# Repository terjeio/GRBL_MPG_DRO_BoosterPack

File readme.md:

## GRBL MPG & DRO BoosterPack for Tiva C \(TM4C123G\) and RP2040 (Pi Pico)

__2024-01-29:__ Added firmware and flasher code for the MSP430 keypad controller to the RP2040 version. This will check for and install/update the firmware automatically.  
Splitted LCD driver code in separate files for each display type supported.

__2022-01-13:__ Added wiring diagram for default key and LED map.

[Default wiring diagram (pdf)](media/Default%20keypad%20and%20LED%20wiring.pdf).  

The latest keypad code allows adding new keymappings at run time, switching between a few predefined ones or creating a new from scratch.

__2022-01-10:__ First preliminary version with Pi Pico support committed. Tiva C \(TM4C123\) version updated for new HAL/APIs.

__2021-08-30: Pi Pico breakout board design__

First batch of boards \(for final design verification\) to be ordered soon.

__2021-05-01: HALification of the code is underway__

A RP2040 driver for [Pi Pico](https://www.raspberrypi.org/products/raspberry-pi-pico/) is nearing completion, watch this space.

__2019-08-20: Improved startup sequence__

The GPIO line used for signalling MPG mode change is now used to signal the grbl controller ready state during startup.

On a cold start the Grbl microcontroller should pull the line low as early in the process as possible.
When the cold start sequence is completed and grbl is ready to receive data the line should be reverted to input mode with interrupt and pullup enabled.
The MPG microcontroller will wait for the line going high before starting any communication, displaying a progress indicator in its boot screen while waiting.

---

Features:

* SPI LCD and touch interface
* Up to two MPG wheels (QEI connected)
* Four GPIO pins, one is preassigned for switching grbl to/from MPG mode
* Up to 8 LEDs, buffered open drain 
* Feed Hold and Cycle Start outputs, open drain
* Up to 25 keys (in matrix)
* Navigator interface
* I2C port (3V3)
* On board MSP430G2553 handling keys and LEDs, internal I2C interface to Tiva C

Parts of alpha-version of supporting code is now available.
An initial commit of the [display driver](https://github.com/terjeio/Display-libraries/) used has now been made public.
The code is written so it is should be easy to port, all processor dependent code is in separate files. 

All core funtionality is now up and running, GUI is 100% event driven making it easy to extend with new dialogs. Shared dialogs (canvases) created for common data (such as DOC, feed rate, RPM), input review/confirmation and GCode transfer to grbl.

### How it works

The setup comprises 3 microcontrollers: one running Grbl, one handling the keyboard scanning and one (the MPG processor) for the DRO and MPG \(user interface\).

#### Grbl/grblHAL microcontroller:

Support for a second input stream and a switch for changing to/from MPG mode has to be added to the code.
In \"normal\" mode the MPG processor listen to the output stream from Grbl, parses the data and displays relevant info on the display.
In \"MPG\" mode Grbl switches its serial input to the second input stream and the MPG prosessor takes over control by acting as a GCode sender.
To tell the MPG processor about a mode change the real time report from Grbl is extended with |MPG:0 \(\"normal\"\) and |MPG:1 \(\"MPG\"\), this is only added when the mode change takes place.
Some of my [grblHAL drivers](https://github.com/grblHAL) supports this functionality as does my [patched version of grbl-Mega](https://github.com/terjeio/grbl-Mega).
 
#### MPG microcontroller:

This handles the user interface \(keypresses, MPG input, menu navigator input and DRO display\). In \"normal\" mode it passively listen to the output stream coming from Grbl, parses it and updates the display and LED statuses accordingly.
For this to work correctly there has to be a PC based GCode sender connected to the controller, such as [ioSender](https://github.com/terjeio/ioSender), that constantly request the real time status report.

In \"MPG\" mode it takes over control and acts as a GCode sender itself, ideally the PC based GCode sender should then disable its GUI.
When turning the MPG wheels G1 commands are issued with a feed rate that is dependent on the turning speed, simulating the action of the handwheels on the lathe.
The jog buttons issues jog commands and most of the other buttons issues real-time commands such as Hold or Cycle start. It is also possible to hardwire some of the button states to the corresponding Grbl input signals.

For the lathe version I am currently working on I am adding canvases \(or dialogs\) that will be used for some simple tasks such as reducing the diameter of the stock, and possibly threading if the Grbl version supports that.
There is a common canvas for streaming task data, this may be used to stream data from a SD card \(not yet implemented\). 

#### Keyboard handling microcontroller:

Due to limited IO on the MPG microcontroller a separate processor is employed for handling the keyboard and LEDs.
Up to 25 keys can be added (in a matrix) and 8 LEDs are supported. Keypresses are sent to the MPG controller via I2C, and there is a strobe signal for telling MPG controller that a key is pressed.
The strobe signal suppports different key modes such as single shot, autorepeat and continuous - configurable per key.

---

### Pi Pico breakout board

---
2021-08-30

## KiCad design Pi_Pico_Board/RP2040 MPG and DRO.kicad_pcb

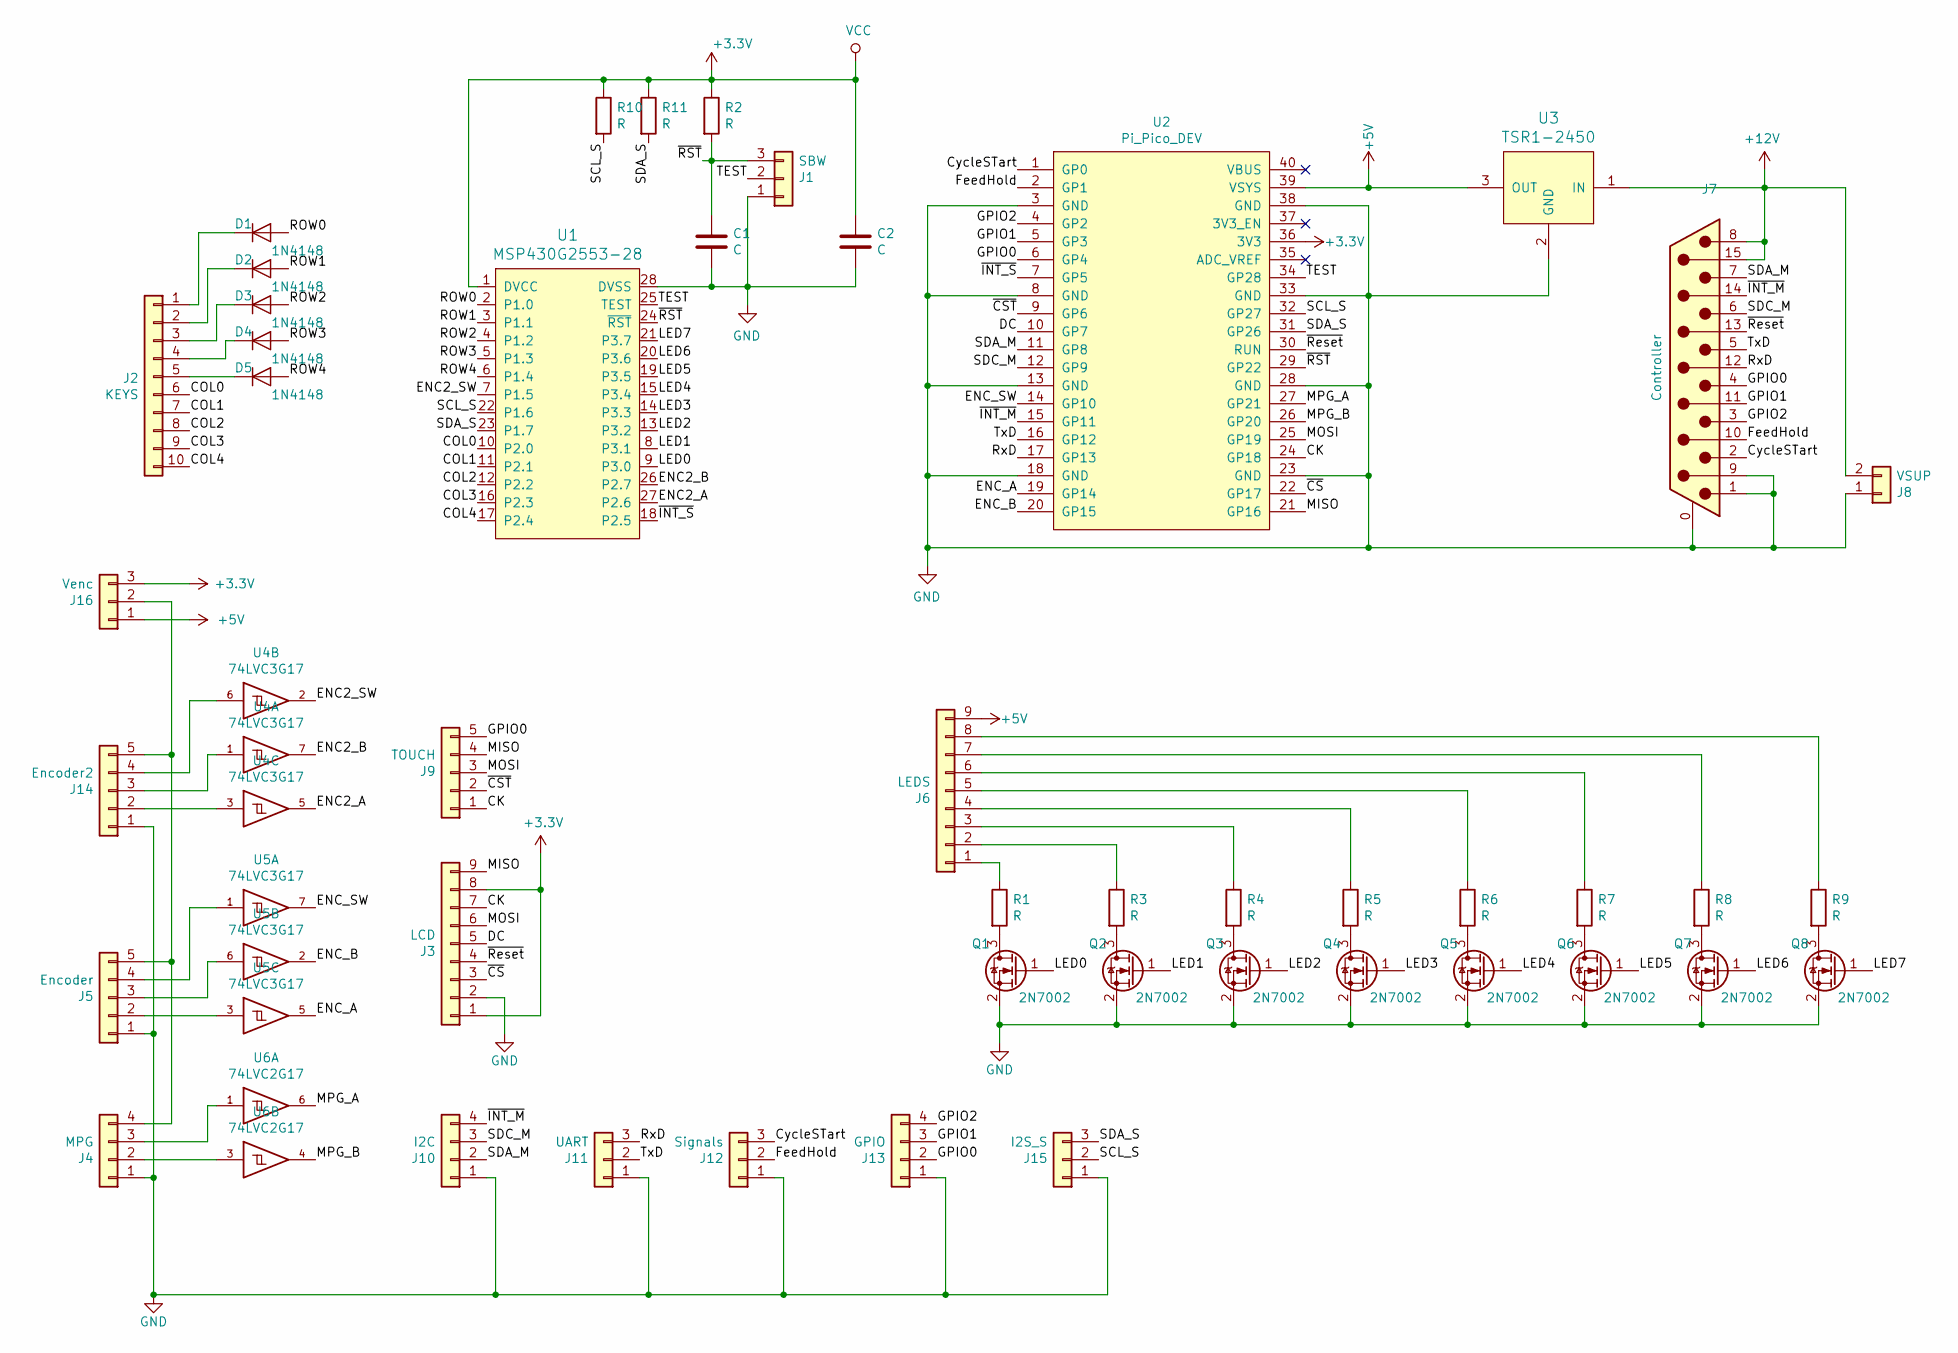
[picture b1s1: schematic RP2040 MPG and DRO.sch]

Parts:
C1, C2: C; C_0805_2012Metric
D1, D2, D3, D4, D5: 1N4148; D_SOD-123
J1: SBW; PinHeader_1x03_P2.54mm_Vertical
J2: KEYS; PinHeader_1x10_P2.54mm_Vertical
J3: LCD; PinHeader_1x09_P2.54mm_Vertical
J4: MPG; PinHeader_1x04_P2.54mm_Vertical
J5: Encoder; PinHeader_1x05_P2.54mm_Vertical
J6: LEDS; PinHeader_1x09_P2.54mm_Vertical
J7: Controller; DB15
J8: VSUP; PinHeader_1x02_P2.54mm_Vertical
J9: TOUCH; PinHeader_1x05_P2.54mm_Vertical
J10: I2C; PinHeader_1x04_P2.54mm_Vertical
J11: UART; PinHeader_1x03_P2.54mm_Vertical
J12: Signals; PinHeader_1x03_P2.54mm_Vertical
J13: GPIO; PinHeader_1x04_P2.54mm_Vertical
J14: Encoder2; PinHeader_1x05_P2.54mm_Vertical
J15: I2S_S; PinHeader_1x03_P2.54mm_Vertical
J16: Venc; PinHeader_1x03_P2.54mm_Vertical
Q1, Q2, Q3, Q4, Q5, Q6, Q7, Q8: 2N7002; SOT-23
R1, R2, R3, R4, R5, R6, R7, R8, R9, R10, R11: R; R_0805_2012Metric
U1: MSP430G2553-28; TSSOP-28_4.4x9.7mm_P0.65mm
U2: Pi_Pico_DEV
U3: TSR1-2450; TSR_1
U4, U5: 74LVC3G17; SSOP-8_2.95x2.8mm_P0.65mm
U6: 74LVC2G17; SOT-23-6

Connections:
+3V3: C2.1, J3.1, J3.8, J16.3, R2.1, R10.1, R11.1, U1.1 (DVCC), U2.36 (3V3), U4.8 (VCC), U5.8 (VCC), U6.5 (VCC)
+5V: J6.9, J16.1, U2.39 (VSYS), U3.3 (OUT)
+12V: J7.8, J7.15, J8.2, U3.1 (IN)
/CK: J3.7, J9.1, U2.24 (GP18)
/COL0: J2.6, U1.10 (P2.0)
/COL1: J2.7, U1.11 (P2.1)
/COL2: J2.8, U1.12 (P2.2)
/COL3: J2.9, U1.16 (P2.3)
/COL4: J2.10, U1.17 (P2.4)
/CycleSTart: J7.2, J12.3, U2.1 (GP0)
/DC: J3.5, U2.10 (GP7)
/ENC2_A: U1.27 (P2.6), U4.5
/ENC2_B: U1.26 (P2.7), U4.7
/ENC2_SW: U1.7 (P1.5), U4.2
/ENC_A: U2.19 (GP14), U5.5
/ENC_B: U2.20 (GP15), U5.2
/ENC_SW: U2.14 (GP10), U5.7
/FeedHold: J7.10, J12.2, U2.2 (GP1)
/GPIO0: J7.4, J9.5, J13.2, U2.6 (GP4)
/GPIO1: J7.11 (P111), J13.3, U2.5 (GP3)
/GPIO2: J7.3, J13.4, U2.4 (GP2)
/LED0: Q1.1 (G), U1.9 (P3.0)
/LED1: Q2.1 (G), U1.8 (P3.1)
/LED2: Q3.1 (G), U1.13 (P3.2)
/LED3: Q4.1 (G), U1.14 (P3.3)
/LED4: Q5.1 (G), U1.15 (P3.4)
/LED5: Q6.1 (G), U1.19 (P3.5)
/LED6: Q7.1 (G), U1.20 (P3.6)
/LED7: Q8.1 (G), U1.21 (P3.7)
/MISO: J3.9, J9.4, U2.21 (GP16)
/MOSI: J3.6, J9.3, U2.25 (GP19)
/MPG_A: U2.27 (GP21), U6.6
/MPG_B: U2.26 (GP20), U6.4
/ROW0: D1.2 (A), U1.2 (P1.0)
/ROW1: D2.2 (A), U1.3 (P1.1)
/ROW2: D3.2 (A), U1.4 (P1.2)
/ROW3: D4.2 (A), U1.5 (P1.3)
/ROW4: D5.2 (A), U1.6 (P1.4)
/RxD: J7.12, J11.3, U2.17 (GP13)
/SCL_S: J15.2, R10.2, U1.22 (P1.6), U2.32 (GP27)
/SDA_M: J7.7, J10.2, U2.11 (GP8)
/SDA_S: J15.3, R11.2, U1.23 (P1.7), U2.31 (GP26)
/SDC_M: J7.6, J10.3, U2.12 (GP9)
/TEST: J1.2, U1.25 (TEST), U2.34 (GP28)
/TxD: J7.5, J11.2, U2.16 (GP12)
/~CS: J3.3, U2.22 (GP17)
/~CST: J9.2, U2.9 (GP6)
/~INT_M: J7.14, J10.4, U2.15 (GP11)
/~INT_S: U1.18 (P2.5), U2.7 (GP5)
/~RST: C1.1, J1.3, R2.2, U1.24 (~RST~), U2.29 (GP22)
/~Reset: J3.4, J7.13, U2.30 (RUN)
GND: C1.2, C2.2, J1.1, J3.2, J4.1, J5.1, J7.0 (PAD), J7.1, J7.9, J8.1, J10.1, J11.1, J12.1, J13.1, J14.1, J15.1, Q1.2 (S), Q2.2 (S), Q3.2 (S), Q4.2 (S), Q5.2 (S), Q6.2 (S), Q7.2 (S), Q8.2 (S), U1.28 (DVSS), U2.3 (GND), U2.8 (GND), U2.13 (GND), U2.18 (GND), U2.23 (GND), U2.28 (GND), U2.33 (GND), U2.38 (GND), U3.2 (GND), U4.4 (GND), U5.4 (GND), U6.2 (GND)
unnamed: D1.1 (K), J2.1
unnamed: D2.1 (K), J2.2
unnamed: D3.1 (K), J2.3
unnamed: D4.1 (K), J2.4
unnamed: D5.1 (K), J2.5
unnamed: J4.2, U6.3
unnamed: J4.3, U6.1
unnamed: J5.2, U5.3
unnamed: J5.3, U5.6
unnamed: J5.4, U5.1
unnamed: J6.1, R1.1
unnamed: J6.2, R3.1
unnamed: J6.3, R4.1
unnamed: J6.4, R5.1
unnamed: J6.5, R6.1
unnamed: J6.6, R7.1
unnamed: J6.7, R8.1
unnamed: J6.8, R9.1
unnamed: J14.2, U4.3
unnamed: J14.3, U4.1
unnamed: J14.4, U4.6
unnamed: J4.4, J5.5, J14.5, J16.2
unnamed: Q1.3 (D), R1.2
unnamed: Q2.3 (D), R3.2
unnamed: Q3.3 (D), R4.2
unnamed: Q4.3 (D), R5.2
unnamed: Q5.3 (D), R6.2
unnamed: Q6.3 (D), R7.2
unnamed: Q7.3 (D), R8.2
unnamed: Q8.3 (D), R9.2

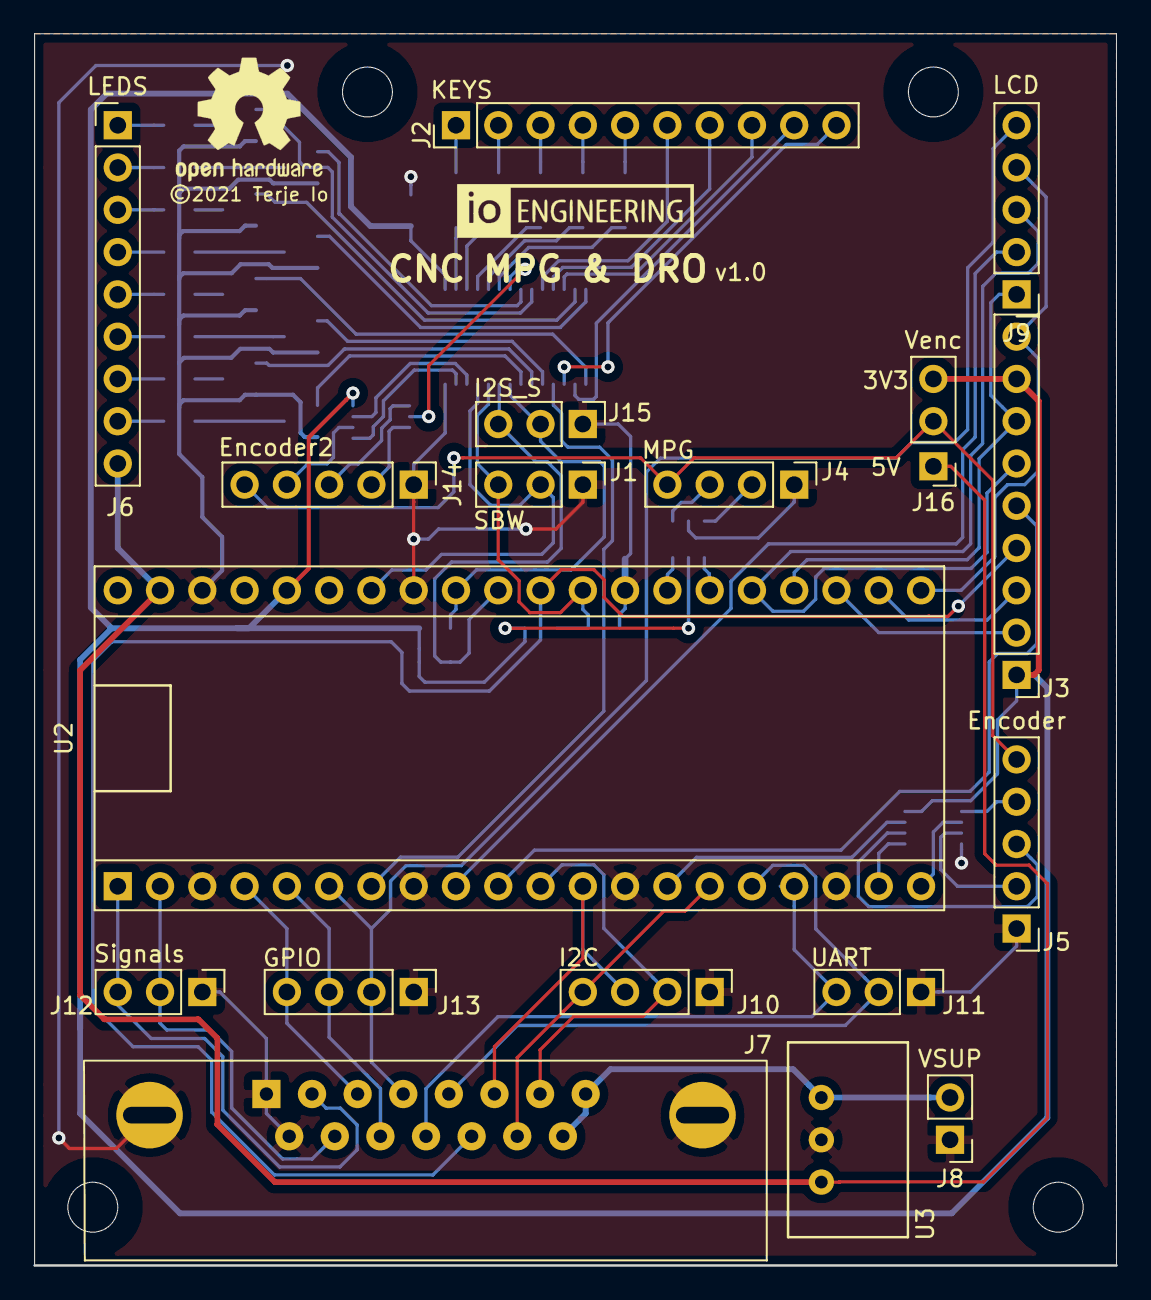
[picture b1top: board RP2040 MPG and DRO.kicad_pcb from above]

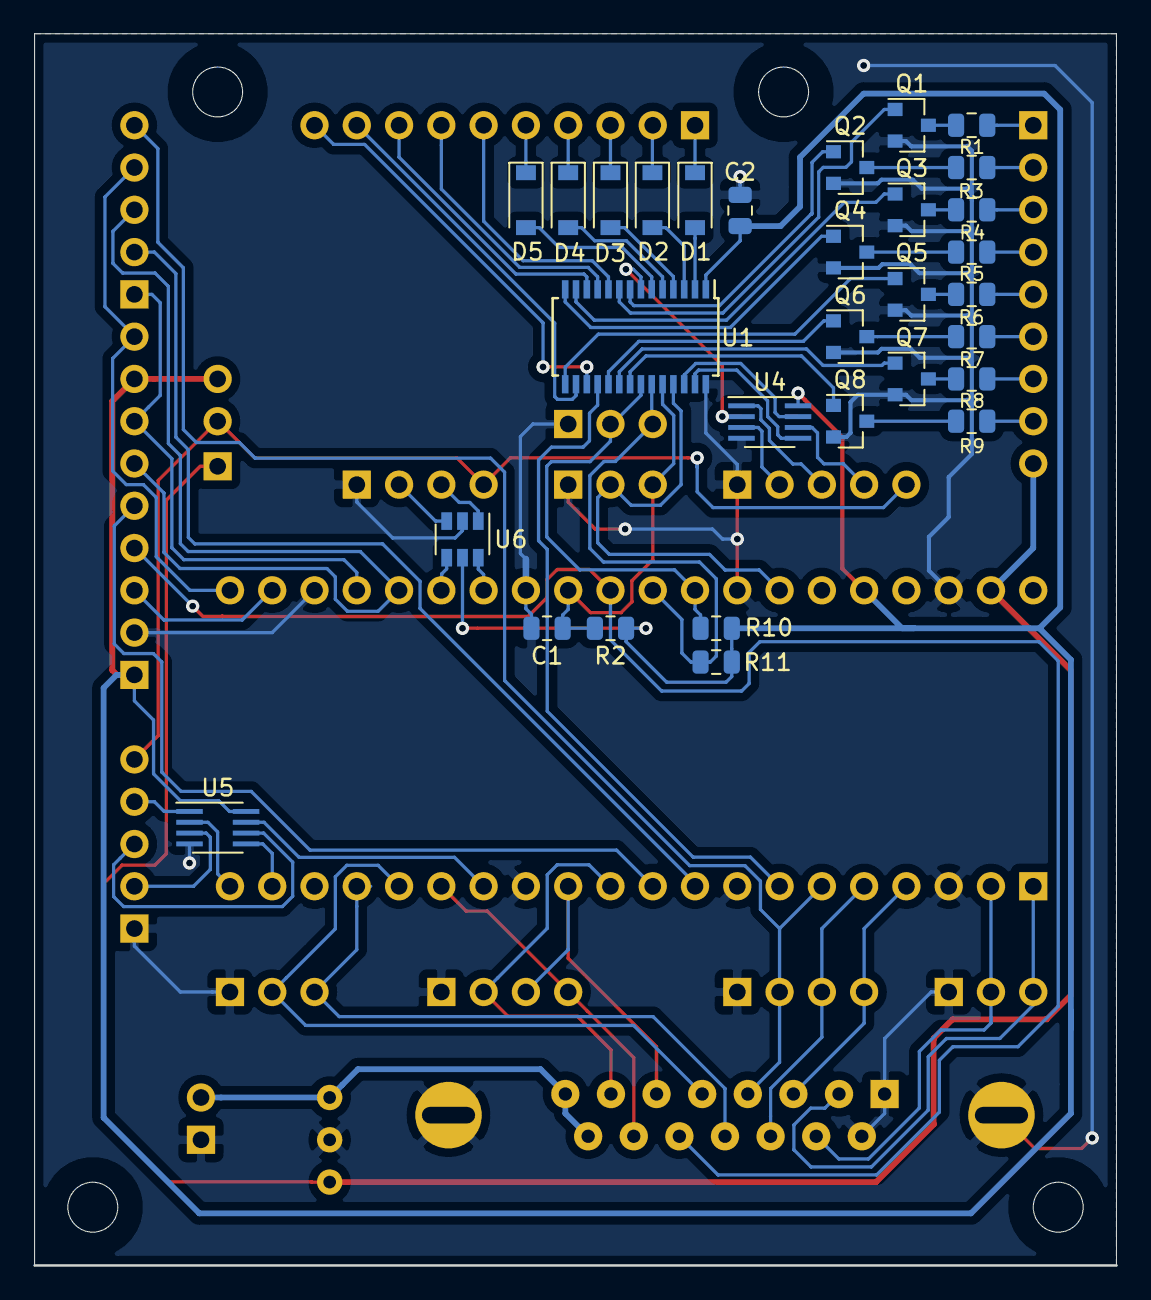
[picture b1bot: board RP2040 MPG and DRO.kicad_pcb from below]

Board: 2 copper layers, 65.0 x 74.0 mm, 48 parts (30 on the bottom side), 82 nets.

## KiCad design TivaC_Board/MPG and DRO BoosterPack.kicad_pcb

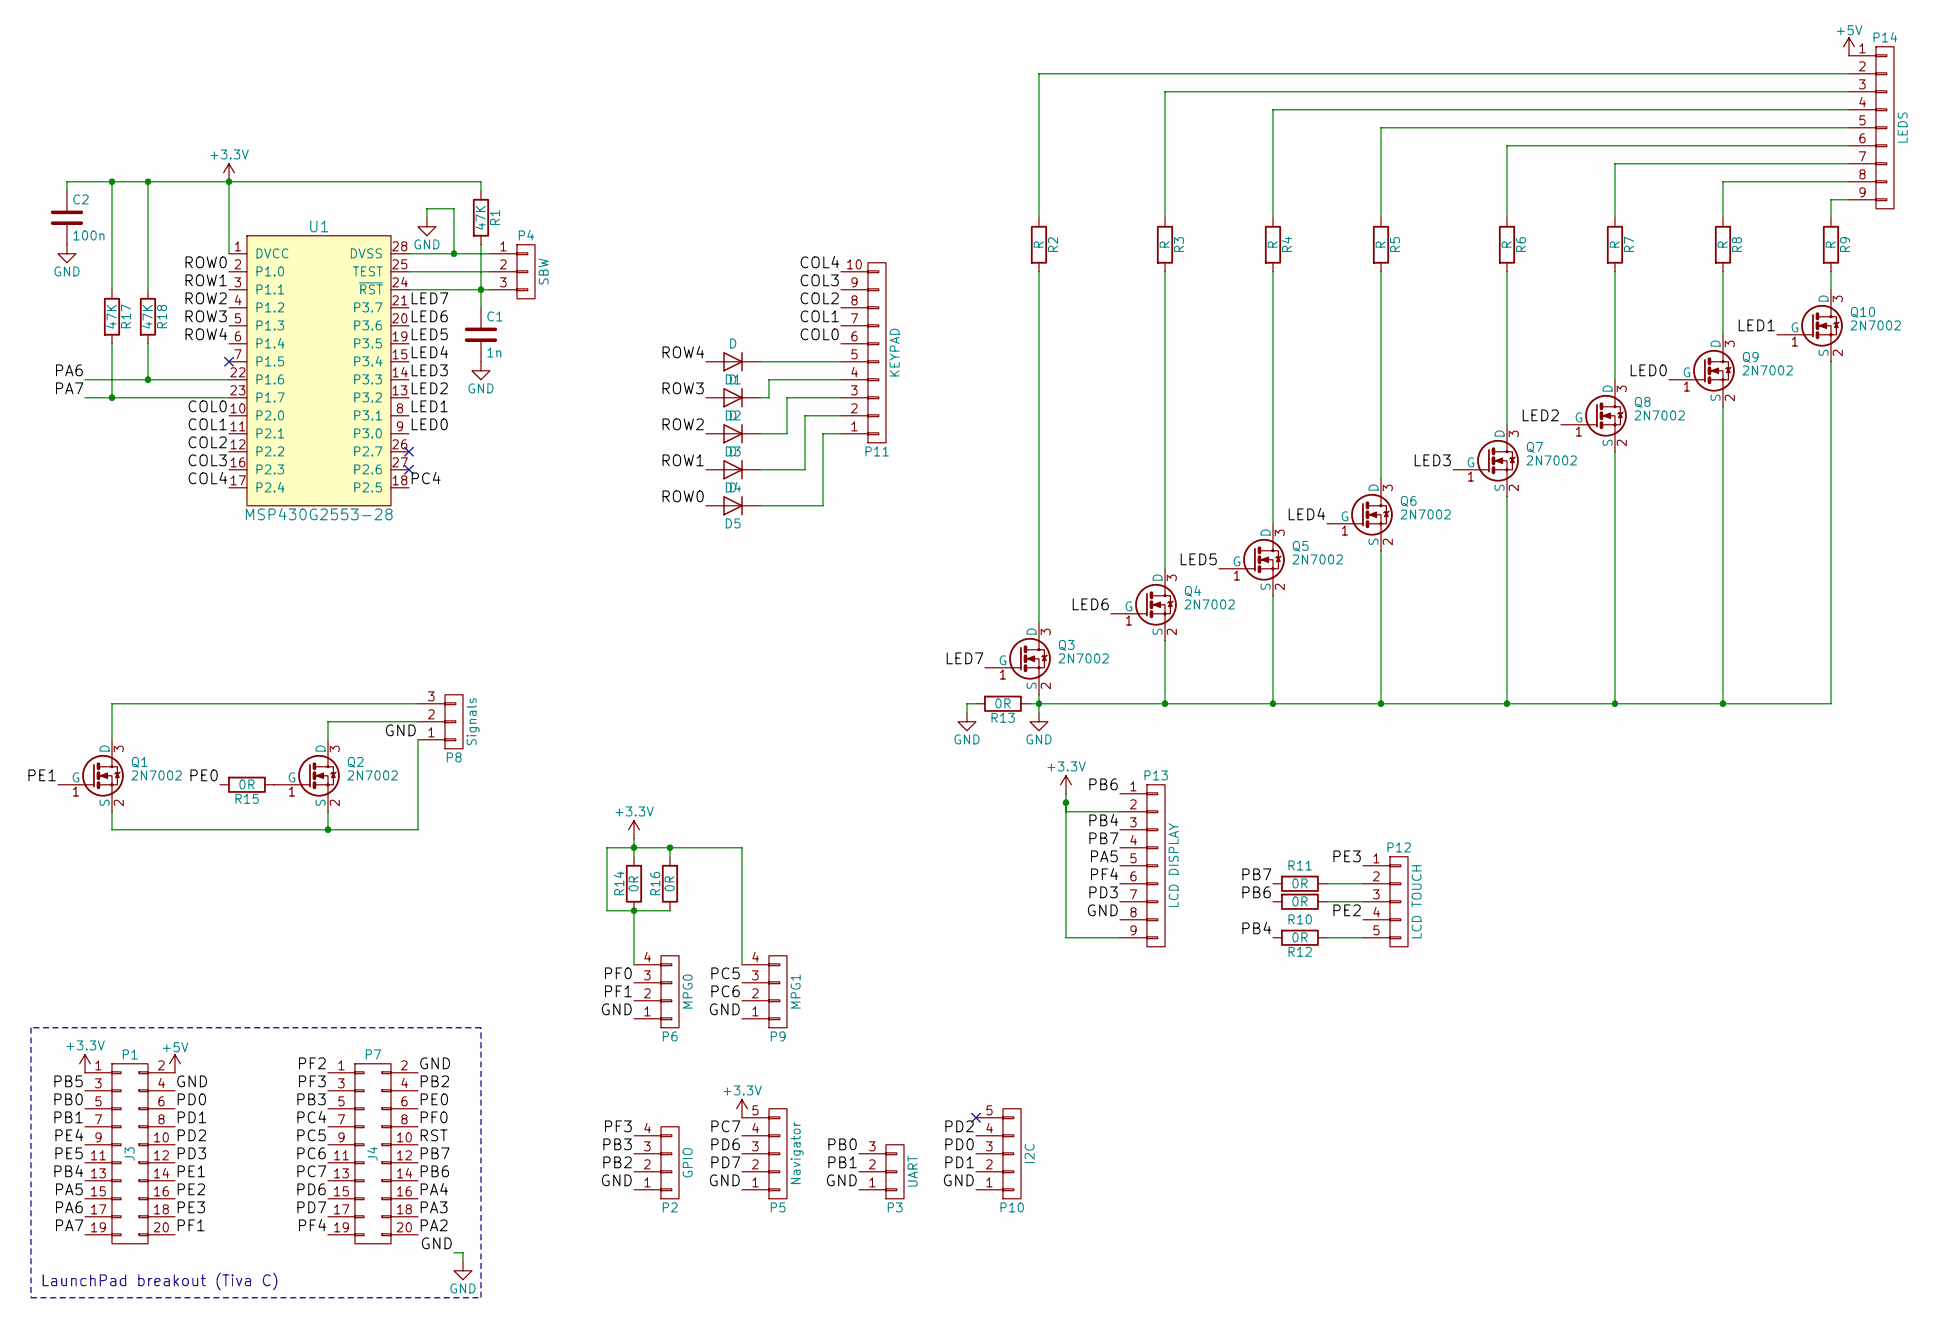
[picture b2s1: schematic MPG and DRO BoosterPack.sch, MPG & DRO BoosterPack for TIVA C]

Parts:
C1: 1n; C_0805
C2: 100n; C_0805
D1, D2, D3, D4, D5: D; D_SOD-123
P1: J3; Socket_Strip_Straight_2x10_SMD
P2: GPIO; Pin_Header_Straight_1x04_Pitch2.54mm
P3: UART; Pin_Header_Straight_1x03_Pitch2.54mm
P4: SBW; Pin_Header_Straight_1x03_Pitch2.54mm
P5: Navigator; Pin_Header_Straight_1x05_Pitch2.54mm
P6: MPG0; Pin_Header_Straight_1x04_Pitch2.54mm
P7: J4; Socket_Strip_Straight_2x10_SMD
P8: Signals; Pin_Header_Straight_1x03_Pitch2.54mm
P9: MPG1; Pin_Header_Straight_1x04_Pitch2.54mm
P10: I2C; Pin_Header_Straight_1x05_Pitch2.54mm
P11: KEYPAD; Pin_Header_Straight_1x10_Pitch2.54mm
P12: LCD TOUCH; Pin_Header_Straight_1x05_Pitch2.54mm
P13: LCD DISPLAY; Pin_Header_Straight_1x09_Pitch2.54mm
P14: LEDS; Pin_Header_Straight_1x09_Pitch2.54mm
Q1, Q2, Q3, Q4, Q5, Q6, Q7, Q8, Q9, Q10: 2N7002; SOT-23
R1, R17, R18: 47K; R_0805
R2, R3, R4, R5, R6, R7, R8, R9: R; R_0805
R10, R11, R12, R13, R14: 0R; R_1206
R15, R16: 0R; R_0805
U1: MSP430G2553-28; TSSOP-28_4.4x9.7mm_Pitch0.65mm

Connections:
+3V3: C2.1, P1.1, P5.5, P6.4, P9.4, P13.2, P13.9, R1.1, R14.1, R14.2, R16.1, R16.2, R17.1, R18.1, U1.1 (DVCC)
+5V: P1.2, P14.1
/COL0: P11.6, U1.10 (P2.0)
/COL1: P11.7, U1.11 (P2.1)
/COL2: P11.8, U1.12 (P2.2)
/COL3: P11.9, U1.16 (P2.3)
/COL4: P11.10, U1.17 (P2.4)
/LED0: Q9.1 (G), U1.9 (P3.0)
/LED1: Q10.1 (G), U1.8 (P3.1)
/LED2: Q8.1 (G), U1.13 (P3.2)
/LED3: Q7.1 (G), U1.14 (P3.3)
/LED4: Q6.1 (G), U1.15 (P3.4)
/LED5: Q5.1 (G), U1.19 (P3.5)
/LED6: Q4.1 (G), U1.20 (P3.6)
/LED7: Q3.1 (G), U1.21 (P3.7)
/PA2: P7.20
/PA3: P7.18
/PA4: P7.16
/PA5: P1.15, P13.5
/PA6: P1.17, R18.2, U1.22 (P1.6)
/PA7: P1.19, R17.2, U1.23 (P1.7)
/PB0: P1.5, P3.3
/PB1: P1.7, P3.2
/PB2: P2.2, P7.4
/PB3: P2.3, P7.5
/PB4: P1.13, P13.3, R12.2
/PB5: P1.3
/PB6: P7.14, P13.1, R10.2
/PB7: P7.12, P13.4, R11.2
/PC4: P7.7, U1.18 (P2.5)
/PC5: P7.9, P9.3
/PC6: P7.11, P9.2
/PC7: P5.4, P7.13
/PD0: P1.6, P10.3
/PD1: P1.8, P10.2
/PD2: P1.10, P10.4
/PD3: P1.12, P13.7
/PD6: P5.3, P7.15
/PD7: P5.2, P7.17
/PE0: P7.6, R15.2
/PE1: P1.14, Q1.1 (G)
/PE2: P1.16, P12.4
/PE3: P1.18, P12.1
/PE4: P1.9
/PE5: P1.11
/PF0: P6.3, P7.8
/PF1: P1.20, P6.2
/PF2: P7.1
/PF3: P2.4, P7.3
/PF4: P7.19, P13.6
/ROW0: D5.2 (A), U1.2 (P1.0)
/ROW1: D4.2 (A), U1.3 (P1.1)
/ROW2: D3.2 (A), U1.4 (P1.2)
/ROW3: D2.2 (A), U1.5 (P1.3)
/ROW4: D1.2 (A), U1.6 (P1.4)
/RST: P7.10
GND: C1.2, C2.2, P1.4, P2.1, P3.1, P4.1, P5.1, P6.1, P7.2, P8.1, P9.1, P10.1, P13.8, Q1.2 (S), Q2.2 (S), Q3.2 (S), Q4.2 (S), Q5.2 (S), Q6.2 (S), Q7.2 (S), Q8.2 (S), Q9.2 (S), Q10.2 (S), R13.1, R13.2, U1.28 (DVSS)
unnamed: C1.1, P4.3, R1.2, U1.24 (~RST~)
unnamed: D1.1 (K), P11.5
unnamed: D2.1 (K), P11.4
unnamed: D3.1 (K), P11.3
unnamed: D4.1 (K), P11.2
unnamed: D5.1 (K), P11.1
unnamed: P4.2, U1.25 (TEST)
unnamed: P8.2, Q2.3 (D)
unnamed: P8.3, Q1.3 (D)
unnamed: P12.2, R11.1
unnamed: P12.3, R10.1
unnamed: P12.5, R12.1
unnamed: P14.2, R2.1
unnamed: P14.3, R3.1
unnamed: P14.4, R4.1
unnamed: P14.5, R5.1
unnamed: P14.6, R6.1
unnamed: P14.7, R7.1
unnamed: P14.8, R8.1
unnamed: P14.9, R9.1
unnamed: Q2.1 (G), R15.1
unnamed: Q3.3 (D), R2.2
unnamed: Q4.3 (D), R3.2
unnamed: Q5.3 (D), R4.2
unnamed: Q6.3 (D), R5.2
unnamed: Q7.3 (D), R6.2
unnamed: Q8.3 (D), R7.2
unnamed: Q9.3 (D), R8.2
unnamed: Q10.3 (D), R9.2

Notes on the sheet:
LaunchPad breakout (Tiva C)

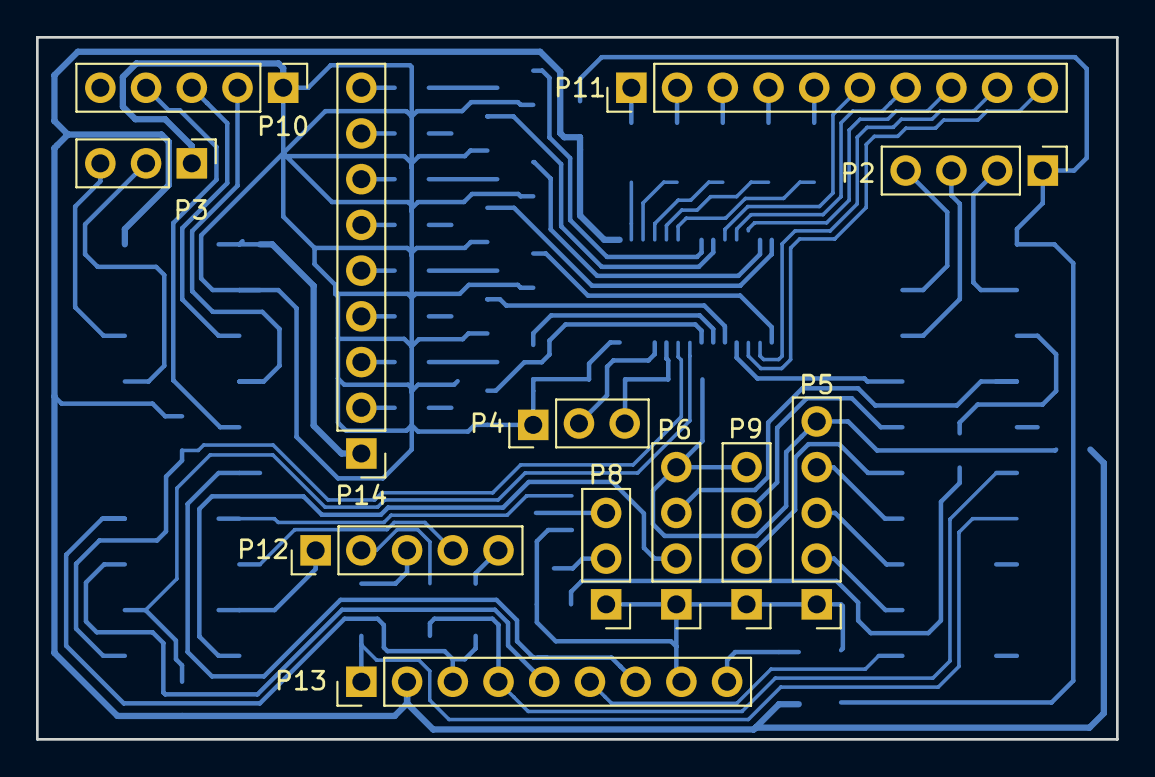
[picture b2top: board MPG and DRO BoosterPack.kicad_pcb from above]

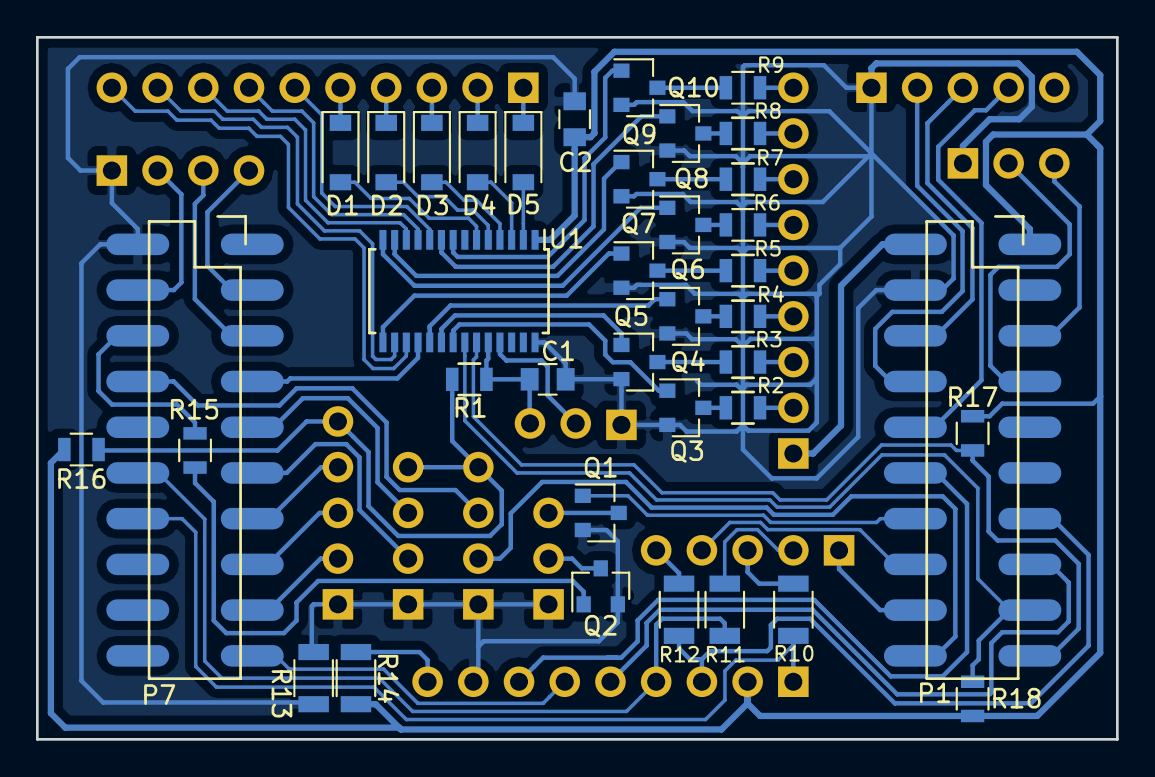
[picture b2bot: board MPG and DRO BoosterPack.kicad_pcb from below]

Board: 2 copper layers, 60.0 x 39.0 mm, 50 parts (38 on the bottom side), 78 nets.

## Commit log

2018-05-03 :lollipop: Added .gitattributes & .gitignore files
2018-05-03 MPG and DRO BoosterPack for Texas Instruments Tiva C
    For eliminating a cable mess and providing ample I/O for keys (buttons)
    and LEDs, has an onboard MSP430G2553 for that.
2018-05-03 Added media file
2018-05-07 Added alpha version of firmware
    Added alpha version of firmware
2018-05-10 Updated
    Added code for keypad processor, updated MPG and DRO code
2018-07-04 Work in progress
    Reorganized code for event driven GUI, added several canvases (screens)
    for functionality in addition to plain DRO & MPG.
2018-07-07 More work in progress
    Dialogs for common parameters, input review. Improved GCode sender (to
    be enhanced)++
2018-09-27 More work in progress...
2018-09-28 Updated readme with some details of the setup
2018-10-17 Added link to required display drivers library
2019-04-17 Some code cleanup, added spindle RPM control
    Spindle RPM can now be adjusted with navigator (Menu encoder) when DRO
    canvas is active. Min/max RPM limits are read from grbl settings on
    connect.
2019-06-03 Many improvements in grbl message parser++
    Some improvements needs my grblHAL port to function correctly as my
    forked vanilla grbl lacks good support for MPG. Among lacking features
    are message output synced to gcode execution and the fact that execution
    continues after an error (until the sender stops transmitting and the
    input buffer is empty - depends on streaming mode). The latest grbHAL
    version (to be updated soon) will return the last error until a reset, a
2019-08-21 Improved startup sequence, added detection/handling of grbl resets.
2019-08-21 Missed one file...
2021-08-30 Added preliminary Pi Pico board design
2021-08-30 Added Pi Pico design files
2022-01-10 Updated to new structure, added RP2040 (Pi Pico) firmware
2022-01-13 Added default keys and LEDs wiring diagram, updated readme
2022-01-30 Work in progress
2023-02-06 Bug fixes, issue #13
2023-02-27 Added pin label for clarity
2024-01-29 Added firmware blob and flasher for the MSP430 keypad controller to the RP2040 version
2025-03-09 Updated to latest version. Fix for changed compiler optimization causing font render failure.

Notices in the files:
PCB/MPG and DRO BoosterPack.sch:
Licensed under CERN OHL v.1.2 or later
Pi_Pico_Board/RP2040 MPG and DRO.kicad_pcb:
©2021 Terje Io
